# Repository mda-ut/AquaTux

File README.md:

AquaTux

Repository for University of Toronto's Mechatronics Design Association, which houses all revision controlled software and hardware for our team's entry into the international RoboSub competition: AquaTux!

See http://www.auvsifoundation.org/foundation/competitions/robosub/ for more detail on the competition. Also, our non revision controlled resources can be found at: https://www.dropbox.com/sh/x1nmdbmocld3edr/AAAKEdywBxVcvkEa93l7Mutga. See http://mda.markharfouche.com for our wiki, which is helpful for getting started with this repo.

Happy swimming!

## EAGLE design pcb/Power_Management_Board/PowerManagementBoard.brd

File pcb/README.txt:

Directory: root
Use: Should hold all the MDA PCB projects
Author: Mark Harfouche
Editors:

Every unique board should have it's own directory.
Updated revisions of an existing board should be kept in originals directory. 

Unlike what Mark had previously stated. We support both EAGLE and ALTIUM for PCB development. Pick your poison. 

Do not commit generated files such as Gerbers unless they are final revisions. 

-- David Biancolin (Dec, 2012)

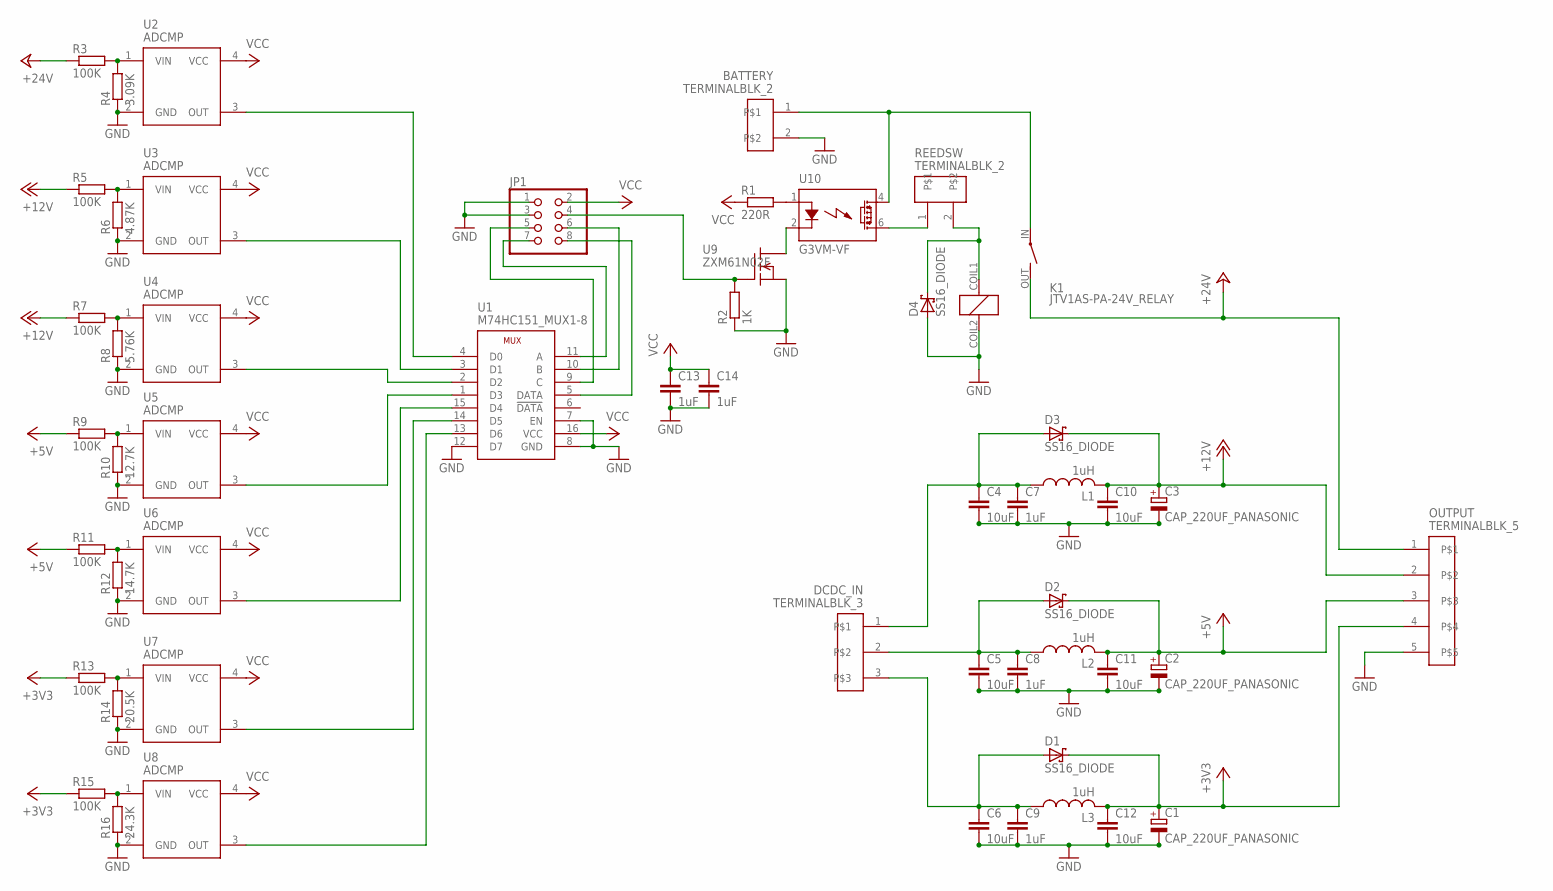
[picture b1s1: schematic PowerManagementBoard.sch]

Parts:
BATTERY: TERMINALBLK_2; TERMINAL_BLK-2
C1, C2, C3: CAP_220UF_PANASONIC
C4, C5, C6, C10, C11, C12: 10uF; C1206
C7, C8, C9, C13, C14: 1uF; C1206
D1, D2, D3, D4: SS16_DIODE; DO214AC
DCDC_IN: TERMINALBLK_3; TERMINAL_BLK-3
JP1: PINHD-2X4; 2X04
K1: JTV1AS-PA-24V_RELAY; JTV-RELAY_FORM1A
L1, L2, L3: 1uH; CHOKE_WE-HCC_8070
OUTPUT: TERMINALBLK_5; TERMINAL_BLK-5
R1: 220R; R0603
R2: 1K; R0603
R3, R5, R7, R9, R11, R13, R15: 100K; R0603
R4: 3.09K; R0603
R6: 4.87K; R0603
R8: 5.76K; R0603
R10: 12.7K; R0603
R12: 14.7K; R0603
R14: 20.5K; R0603
R16: 24.3K; R0603
REEDSW: TERMINALBLK_2; TERMINAL_BLK-2
U1: M74HC151_MUX1-8; TSSOP16
U2, U3, U4, U5, U6, U7, U8: ADCMP; SC70-4
U9: ZXM61N02F; SOT23W
U10: G3VM-VF

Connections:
+3V3: C1.P (+), C12.1, D1.C, L3.P$2 (2), OUTPUT.4, R13.1, R15.1
+5V: C2.P (+), C11.1, D2.C, L2.P$2 (2), OUTPUT.3, R9.1, R11.1
+12V: C3.P (+), C10.1, D3.C, L1.P$2 (2), OUTPUT.2, R5.1, R7.1
+24V: K1.OUT (S), OUTPUT.1, R3.1
GND: BATTERY.2, C1.N (-), C2.N (-), C3.N (-), C4.2, C5.2, C6.2, C7.2, C8.2, C9.2, C10.2, C11.2, C12.2, C13.2, C14.2, D4.A, JP1.1, JP1.3, K1.COIL2 (2), OUTPUT.5, R2.1, R4.1, R6.1, R8.1, R10.1, R12.1, R14.1, R16.1, U1.7 (EN), U1.8 (GND), U1.12 (D7), U2.2 (GND), U3.2 (GND), U4.2 (GND), U5.2 (GND), U6.2 (GND), U7.2 (GND), U8.2 (GND), U9.2 (S)
unnamed: BATTERY.1, K1.IN, U10.4 (DS1)
unnamed: REEDSW.1, U10.6 (DS2)
unnamed: D4.C, K1.COIL1 (1), REEDSW.2
unnamed: C6.1, C9.1, D1.A, DCDC_IN.3, L3.P$1 (1)
unnamed: C5.1, C8.1, D2.A, DCDC_IN.2, L2.P$1 (1)
unnamed: C4.1, C7.1, D3.A, DCDC_IN.1, L1.P$1 (1)
unnamed: U9.3 (D), U10.2 (K)
unnamed: R1.2, U10.1 (A)
unnamed: JP1.4, R2.2, U9.1 (G)
unnamed: JP1.8, U1.5 (DATA)
unnamed: JP1.6, U1.10 (B)
unnamed: JP1.7, U1.11 (A)
unnamed: JP1.5, U1.9 (C)
unnamed: R3.2, R4.2, U2.1 (VIN)
unnamed: R5.2, R6.2, U3.1 (VIN)
unnamed: R7.2, R8.2, U4.1 (VIN)
unnamed: R9.2, R10.2, U5.1 (VIN)
unnamed: R11.2, R12.2, U6.1 (VIN)
unnamed: R13.2, R14.2, U7.1 (VIN)
unnamed: R15.2, R16.2, U8.1 (VIN)
unnamed: U1.4 (D0), U2.3 (OUT)
unnamed: U1.3 (D1), U3.3 (OUT)
unnamed: U1.2 (D2), U4.3 (OUT)
unnamed: U1.1 (D3), U5.3 (OUT)
unnamed: U1.15 (D4), U6.3 (OUT)
unnamed: U1.14 (D5), U7.3 (OUT)
unnamed: U1.13 (D6), U8.3 (OUT)
VCC: C13.1, C14.1, JP1.2, R1.1, U1.16 (VCC), U2.4 (VCC), U3.4 (VCC), U4.4 (VCC), U5.4 (VCC), U6.4 (VCC), U7.4 (VCC), U8.4 (VCC)

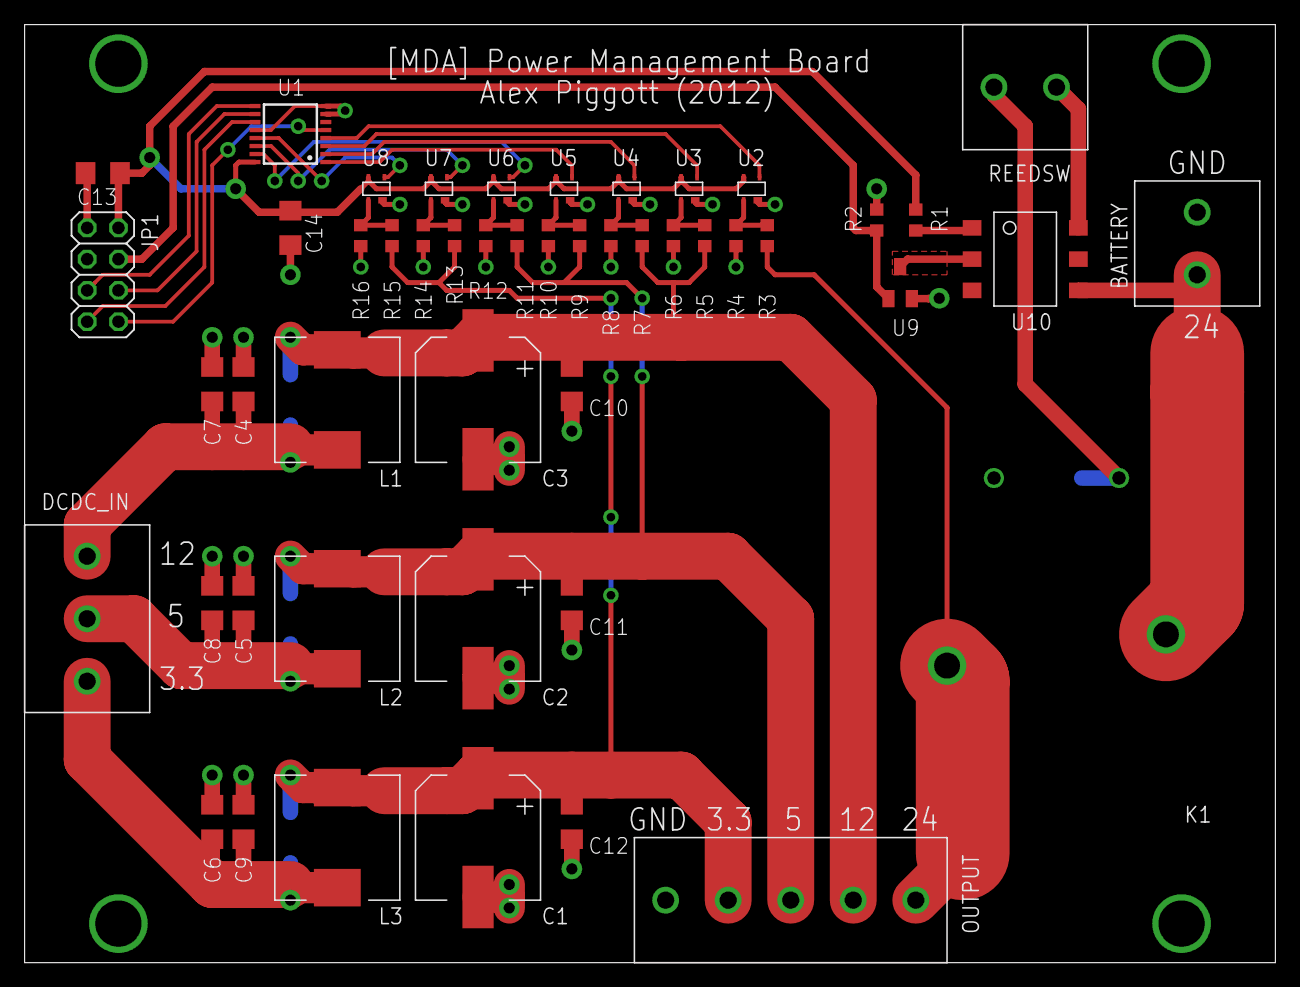
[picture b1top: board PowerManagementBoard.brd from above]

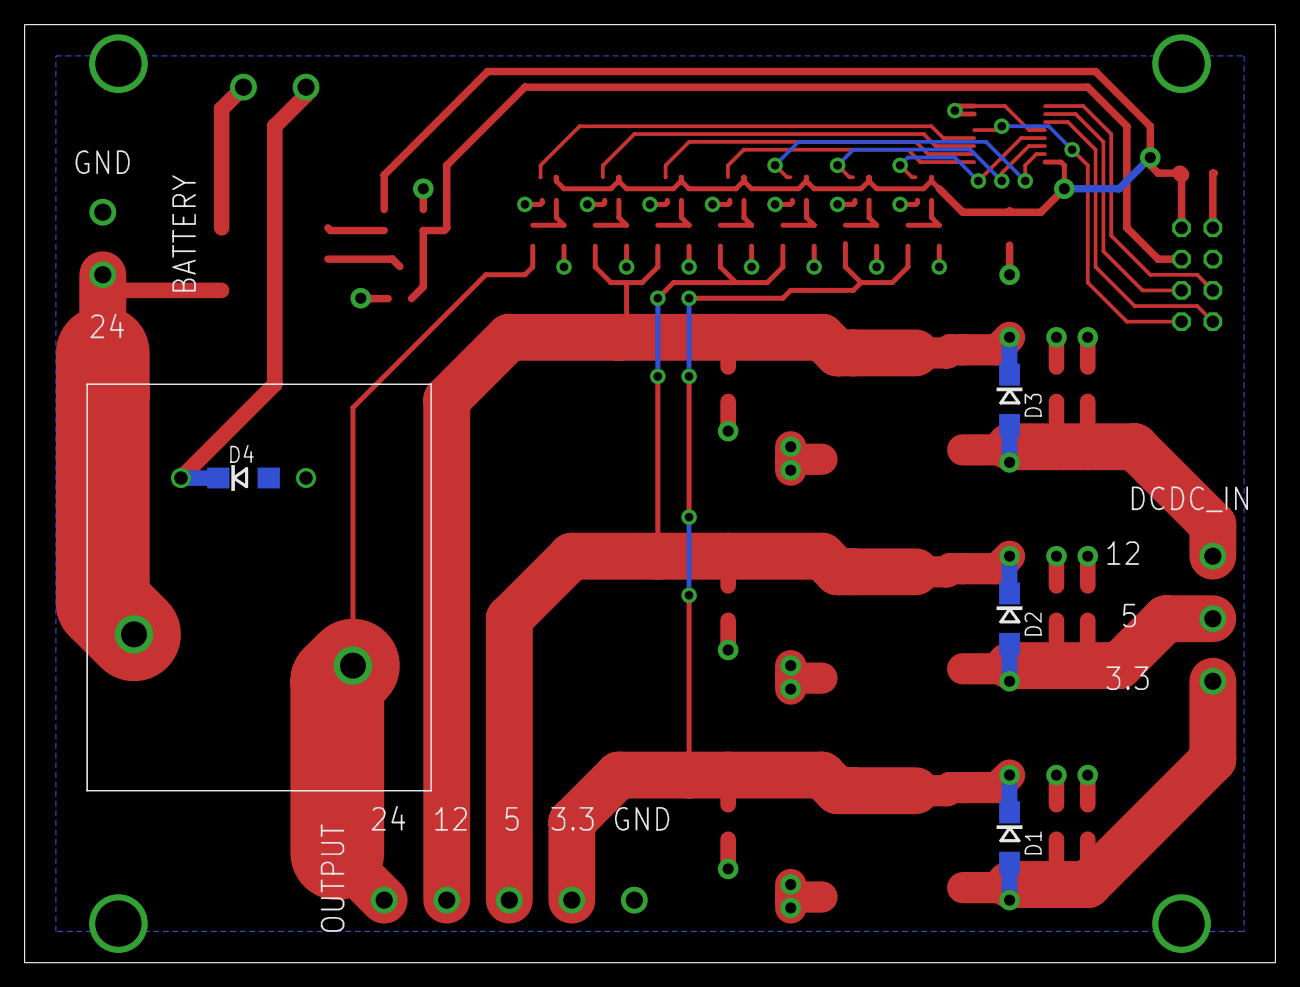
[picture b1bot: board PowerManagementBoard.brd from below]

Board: 2 copper layers, 101.6 x 76.2 mm, 53 parts (4 on the bottom side), 33 nets.

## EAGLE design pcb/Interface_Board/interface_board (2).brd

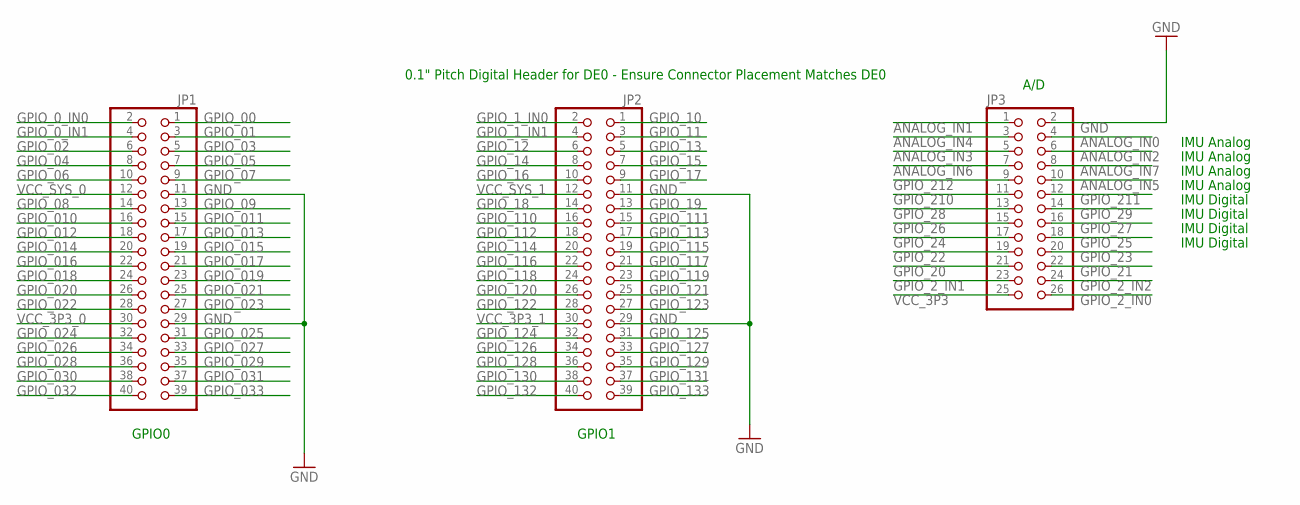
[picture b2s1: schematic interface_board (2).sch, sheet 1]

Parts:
JP1, JP2: PINHD-2X20; 2X20
JP3: PINHD-2X13; 2X13

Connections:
ANALOG_IN0: JP3.4; also elsewhere on the board
ANALOG_IN1: JP3.1; also elsewhere on the board
ANALOG_IN2: JP3.6; also elsewhere on the board
ANALOG_IN3: JP3.5; also elsewhere on the board
ANALOG_IN4: JP3.3; also elsewhere on the board
ANALOG_IN5: JP3.10; also elsewhere on the board
ANALOG_IN6: JP3.7; also elsewhere on the board
ANALOG_IN7: JP3.8; also elsewhere on the board
GND: JP1.11, JP1.29, JP2.11, JP2.29, JP3.2; also elsewhere on the board
GPIO_00: JP1.1; also elsewhere on the board
GPIO_0_IN0: JP1.2; also elsewhere on the board
GPIO_0_IN1: JP1.4; also elsewhere on the board
GPIO_01: JP1.3; also elsewhere on the board
GPIO_1_IN0: JP2.2; also elsewhere on the board
GPIO_1_IN1: JP2.4; also elsewhere on the board
GPIO_02: JP1.6; also elsewhere on the board
GPIO_2_IN0: JP3.26; also elsewhere on the board
GPIO_2_IN1: JP3.23; also elsewhere on the board
GPIO_2_IN2: JP3.24; also elsewhere on the board
GPIO_03: JP1.5; also elsewhere on the board
GPIO_04: JP1.8; also elsewhere on the board
GPIO_05: JP1.7; also elsewhere on the board
GPIO_06: JP1.10; also elsewhere on the board
GPIO_07: JP1.9; also elsewhere on the board
GPIO_08: JP1.14; also elsewhere on the board
GPIO_09: JP1.13; also elsewhere on the board
GPIO_010: JP1.16; also elsewhere on the board
GPIO_10: JP2.1; also elsewhere on the board
GPIO_011: JP1.15; also elsewhere on the board
GPIO_11: JP2.3; also elsewhere on the board
GPIO_012: JP1.18; also elsewhere on the board
GPIO_12: JP2.6; also elsewhere on the board
GPIO_013: JP1.17; also elsewhere on the board
GPIO_13: JP2.5; also elsewhere on the board
GPIO_014: JP1.20; also elsewhere on the board
GPIO_14: JP2.8; also elsewhere on the board
GPIO_015: JP1.19; also elsewhere on the board
GPIO_15: JP2.7; also elsewhere on the board
GPIO_016: JP1.22; also elsewhere on the board
GPIO_16: JP2.10; also elsewhere on the board
GPIO_017: JP1.21; also elsewhere on the board
GPIO_17: JP2.9; also elsewhere on the board
GPIO_018: JP1.24; also elsewhere on the board
GPIO_18: JP2.14; also elsewhere on the board
GPIO_019: JP1.23; also elsewhere on the board
GPIO_19: JP2.13; also elsewhere on the board
GPIO_020: JP1.26; also elsewhere on the board
GPIO_20: JP3.21; also elsewhere on the board
GPIO_021: JP1.25; also elsewhere on the board
GPIO_21: JP3.22; also elsewhere on the board
GPIO_022: JP1.28; also elsewhere on the board
GPIO_22: JP3.19; also elsewhere on the board
GPIO_023: JP1.27; also elsewhere on the board
GPIO_23: JP3.20; also elsewhere on the board
GPIO_024: JP1.32; also elsewhere on the board
GPIO_24: JP3.17; also elsewhere on the board
GPIO_025: JP1.31; also elsewhere on the board
GPIO_25: JP3.18; also elsewhere on the board
GPIO_026: JP1.34; also elsewhere on the board
GPIO_26: JP3.15; also elsewhere on the board
GPIO_027: JP1.33; also elsewhere on the board
GPIO_27: JP3.16; also elsewhere on the board
GPIO_028: JP1.36; also elsewhere on the board
GPIO_28: JP3.13; also elsewhere on the board
GPIO_029: JP1.35; also elsewhere on the board
GPIO_29: JP3.14; also elsewhere on the board
GPIO_030: JP1.38; also elsewhere on the board
GPIO_031: JP1.37; also elsewhere on the board
GPIO_032: JP1.40; also elsewhere on the board
GPIO_033: JP1.39; also elsewhere on the board
GPIO_110: JP2.16; also elsewhere on the board
GPIO_111: JP2.15; also elsewhere on the board
GPIO_112: JP2.18; also elsewhere on the board
GPIO_113: JP2.17; also elsewhere on the board
GPIO_114: JP2.20; also elsewhere on the board
GPIO_115: JP2.19; also elsewhere on the board
GPIO_116: JP2.22; also elsewhere on the board
GPIO_117: JP2.21; also elsewhere on the board
GPIO_118: JP2.24; also elsewhere on the board
GPIO_119: JP2.23; also elsewhere on the board
GPIO_120: JP2.26; also elsewhere on the board
GPIO_121: JP2.25; also elsewhere on the board
GPIO_122: JP2.28; also elsewhere on the board
GPIO_123: JP2.27; also elsewhere on the board
GPIO_124: JP2.32; also elsewhere on the board
GPIO_125: JP2.31; also elsewhere on the board
GPIO_126: JP2.34; also elsewhere on the board
GPIO_127: JP2.33; also elsewhere on the board
GPIO_128: JP2.36; also elsewhere on the board
GPIO_129: JP2.35; also elsewhere on the board
GPIO_130: JP2.38; also elsewhere on the board
GPIO_131: JP2.37; also elsewhere on the board
GPIO_132: JP2.40; also elsewhere on the board
GPIO_133: JP2.39; also elsewhere on the board
GPIO_210: JP3.11; also elsewhere on the board
GPIO_211: JP3.12; also elsewhere on the board
GPIO_212: JP3.9; also elsewhere on the board
VCC_3P3: JP3.25; also elsewhere on the board
VCC_3P3_0: JP1.30
VCC_3P3_1: JP2.30; also elsewhere on the board
VCC_SYS_0: JP1.12
VCC_SYS_1: JP2.12

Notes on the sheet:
0.1" Pitch Digital Header for DE0 - Ensure Connector Placement Matches DE0
GPIO0
GPIO1
A/D
IMU Analog
IMU Digital

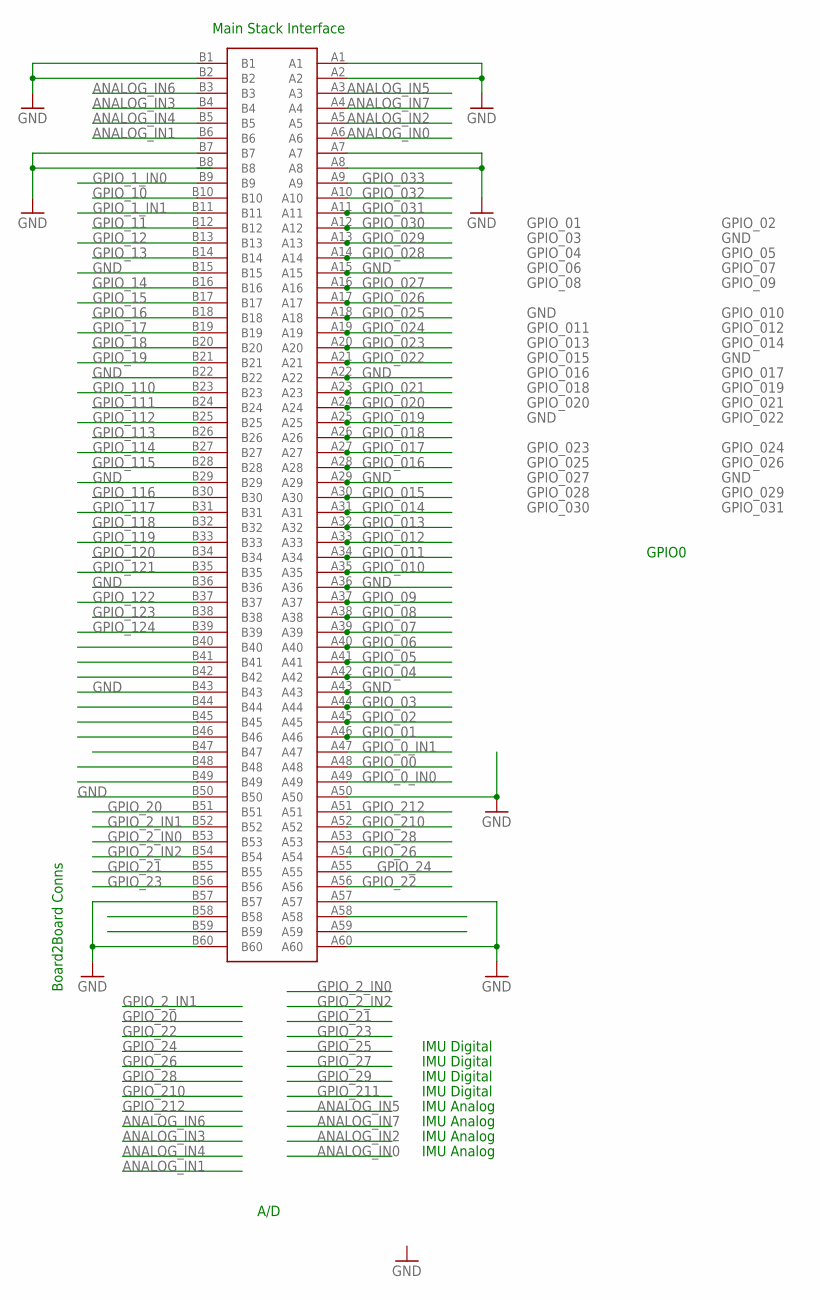
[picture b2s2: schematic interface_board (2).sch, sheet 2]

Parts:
U$10: MAIN-STACK-CONN-WIDEPITCH; STACK-CONN-WIDEPITCH

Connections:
ANALOG_IN0: U$10.A6; also elsewhere on the board
ANALOG_IN1: U$10.B6; also elsewhere on the board
ANALOG_IN2: U$10.A5; also elsewhere on the board
ANALOG_IN3: U$10.B4; also elsewhere on the board
ANALOG_IN4: U$10.B5; also elsewhere on the board
ANALOG_IN5: U$10.A3; also elsewhere on the board
ANALOG_IN6: U$10.B3; also elsewhere on the board
ANALOG_IN7: U$10.A4; also elsewhere on the board
GND: U$10.A1, U$10.A2, U$10.A7, U$10.A8, U$10.A15, U$10.A22, U$10.A29, U$10.A36, U$10.A43, U$10.A50, U$10.A57, U$10.A60, U$10.B1, U$10.B2, U$10.B7, U$10.B15, U$10.B22, U$10.B29, U$10.B36, U$10.B43, U$10.B50, U$10.B57, U$10.B60; also elsewhere on the board
GPIO_00: U$10.A48; also elsewhere on the board
GPIO_0_IN0: U$10.A49; also elsewhere on the board
GPIO_0_IN1: U$10.A47; also elsewhere on the board
GPIO_01: U$10.A46; also elsewhere on the board
GPIO_1_IN0: U$10.B9; also elsewhere on the board
GPIO_1_IN1: U$10.B11; also elsewhere on the board
GPIO_02: U$10.A45; also elsewhere on the board
GPIO_2_IN0: U$10.B53; also elsewhere on the board
GPIO_2_IN1: U$10.B52; also elsewhere on the board
GPIO_2_IN2: U$10.B54; also elsewhere on the board
GPIO_03: U$10.A44; also elsewhere on the board
GPIO_04: U$10.A42; also elsewhere on the board
GPIO_05: U$10.A41; also elsewhere on the board
GPIO_06: U$10.A40; also elsewhere on the board
GPIO_07: U$10.A39; also elsewhere on the board
GPIO_08: U$10.A38; also elsewhere on the board
GPIO_09: U$10.A37; also elsewhere on the board
GPIO_010: U$10.A35; also elsewhere on the board
GPIO_10: U$10.B10; also elsewhere on the board
GPIO_011: U$10.A34; also elsewhere on the board
GPIO_11: U$10.B12; also elsewhere on the board
GPIO_012: U$10.A33; also elsewhere on the board
GPIO_12: U$10.B13; also elsewhere on the board
GPIO_013: U$10.A32; also elsewhere on the board
GPIO_13: U$10.B14; also elsewhere on the board
GPIO_014: U$10.A31; also elsewhere on the board
GPIO_14: U$10.B16; also elsewhere on the board
GPIO_015: U$10.A30; also elsewhere on the board
GPIO_15: U$10.B17; also elsewhere on the board
GPIO_016: U$10.A28; also elsewhere on the board
GPIO_16: U$10.B18; also elsewhere on the board
GPIO_017: U$10.A27; also elsewhere on the board
GPIO_17: U$10.B19; also elsewhere on the board
GPIO_018: U$10.A26; also elsewhere on the board
GPIO_18: U$10.B20; also elsewhere on the board
GPIO_019: U$10.A25; also elsewhere on the board
GPIO_19: U$10.B21; also elsewhere on the board
GPIO_020: U$10.A24; also elsewhere on the board
GPIO_20: U$10.B51; also elsewhere on the board
GPIO_021: U$10.A23; also elsewhere on the board
GPIO_21: U$10.B55; also elsewhere on the board
GPIO_022: U$10.A21; also elsewhere on the board
GPIO_22: U$10.A56; also elsewhere on the board
GPIO_023: U$10.A20; also elsewhere on the board
GPIO_23: U$10.B56; also elsewhere on the board
GPIO_024: U$10.A19; also elsewhere on the board
GPIO_24: U$10.A55; also elsewhere on the board
GPIO_025: U$10.A18; also elsewhere on the board
GPIO_026: U$10.A17; also elsewhere on the board
GPIO_26: U$10.A54; also elsewhere on the board
GPIO_027: U$10.A16; also elsewhere on the board
GPIO_028: U$10.A14; also elsewhere on the board
GPIO_28: U$10.A53; also elsewhere on the board
GPIO_029: U$10.A13; also elsewhere on the board
GPIO_030: U$10.A12; also elsewhere on the board
GPIO_031: U$10.A11; also elsewhere on the board
GPIO_032: U$10.A10; also elsewhere on the board
GPIO_033: U$10.A9; also elsewhere on the board
GPIO_110: U$10.B23; also elsewhere on the board
GPIO_111: U$10.B24; also elsewhere on the board
GPIO_112: U$10.B25; also elsewhere on the board
GPIO_113: U$10.B26; also elsewhere on the board
GPIO_114: U$10.B27; also elsewhere on the board
GPIO_115: U$10.B28; also elsewhere on the board
GPIO_116: U$10.B30; also elsewhere on the board
GPIO_117: U$10.B31; also elsewhere on the board
GPIO_118: U$10.B32; also elsewhere on the board
GPIO_119: U$10.B33; also elsewhere on the board
GPIO_120: U$10.B34; also elsewhere on the board
GPIO_121: U$10.B35; also elsewhere on the board
GPIO_122: U$10.B37; also elsewhere on the board
GPIO_123: U$10.B38; also elsewhere on the board
GPIO_124: U$10.B39; also elsewhere on the board
GPIO_210: U$10.A52; also elsewhere on the board
GPIO_212: U$10.A51; also elsewhere on the board

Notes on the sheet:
Main Stack Interface
GPIO0
A/D
IMU Analog
IMU Digital
Board2Board Conns

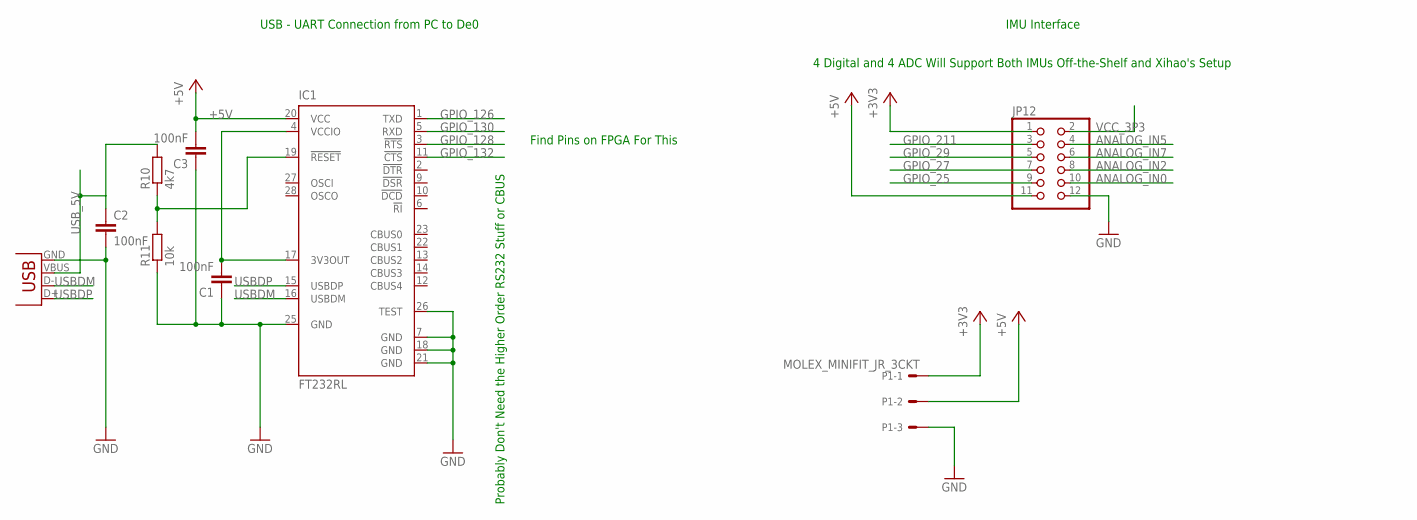
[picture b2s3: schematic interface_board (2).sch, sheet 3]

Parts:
C1, C2, C3: 100nF; C0805
IC1: FT232RL; SSOP28
JP12: PINHD-2X6; 2X06
P1: MOLEX_MINIFIT_JR_3CKT; 3CKT_MINIFIT_JR
R10: 4k7; M0805
R11: 10k; M0805
X1: USBSMD; USB-MINIB

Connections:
+3V3: JP12.1, P1.1; also elsewhere on the board
+5V: C3.2, IC1.20 (VCC), JP12.11, P1.2
ANALOG_IN0: JP12.10; also elsewhere on the board
ANALOG_IN2: JP12.8; also elsewhere on the board
ANALOG_IN5: JP12.4; also elsewhere on the board
ANALOG_IN7: JP12.6; also elsewhere on the board
GND: C1.1, C2.2, C3.1, IC1.7 (GND), IC1.18 (GND), IC1.21 (GND), IC1.25 (GND), IC1.26 (TEST), JP12.12, P1.3, R11.1, X1.GND; also elsewhere on the board
GPIO_25: JP12.9; also elsewhere on the board
GPIO_27: JP12.7; also elsewhere on the board
GPIO_29: JP12.5; also elsewhere on the board
GPIO_126: IC1.1 (TXD); also elsewhere on the board
GPIO_128: IC1.3 (!RTS); also elsewhere on the board
GPIO_130: IC1.5 (RXD); also elsewhere on the board
GPIO_132: IC1.11 (!CTS); also elsewhere on the board
GPIO_211: JP12.3; also elsewhere on the board
unnamed: C1.2, IC1.4 (VCCIO), IC1.17 (3V3OUT)
unnamed: IC1.19 (!RESET), R10.1, R11.2
USBDM: IC1.16 (USBDM), X1.D-
USBDP: IC1.15 (USBDP), X1.D+
USB_5V: C2.1, R10.2, X1.VBUS
VCC_3P3: JP12.2; also elsewhere on the board

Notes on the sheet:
USB - UART Connection from PC to De0
IMU Interface
Probably Don't Need the Higher Order RS232 Stuff or CBUS
Find Pins on FPGA For This
4 Digital and 4 ADC Will Support Both IMUs Off-the-Shelf and Xihao's Setup

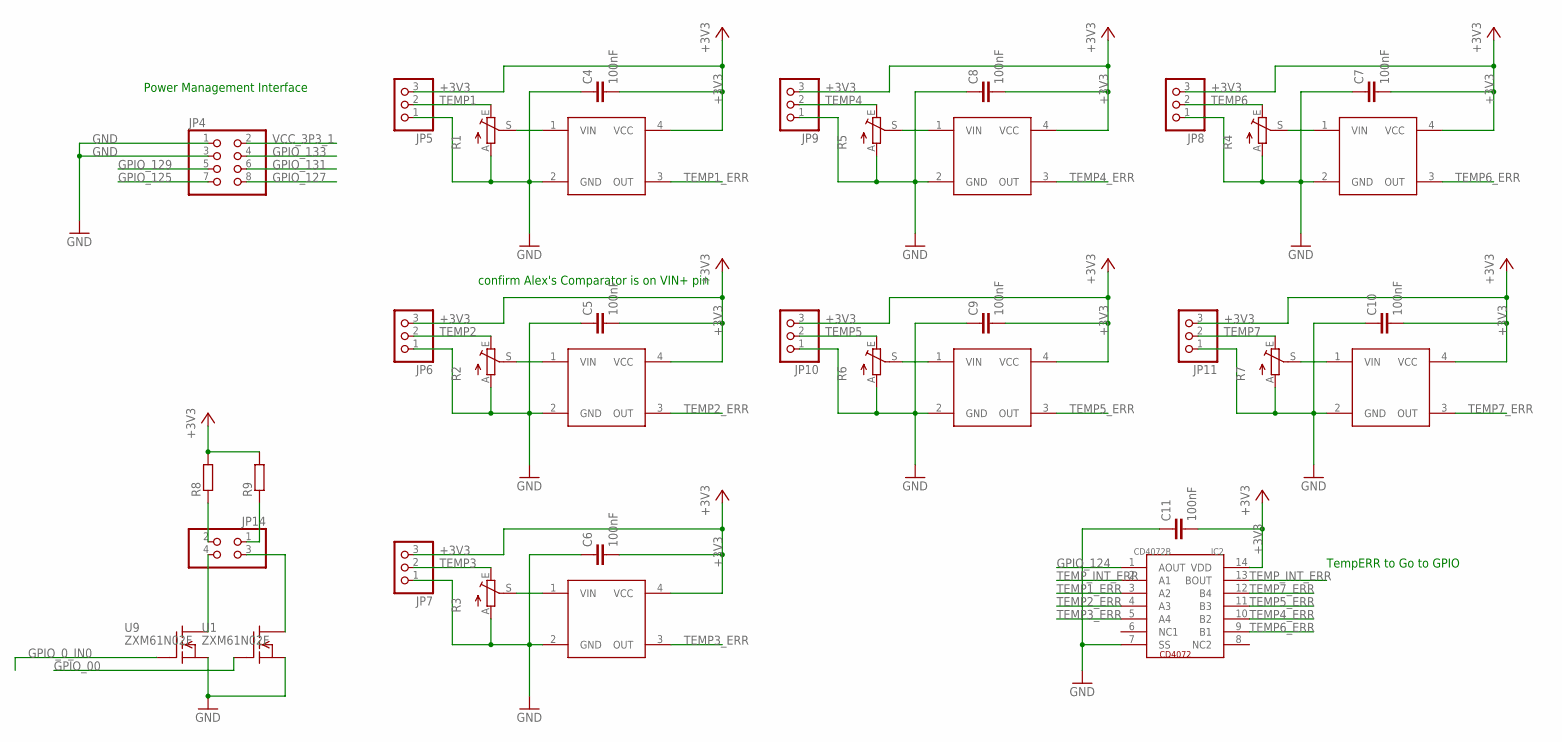
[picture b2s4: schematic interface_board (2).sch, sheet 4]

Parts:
C4, C5, C6, C7, C8, C9, C10, C11: 100nF; C0805
IC2: CD4072B; SO14
JP4: PINHD-2X4; 2X04
JP5, JP6, JP7, JP8, JP9, JP10, JP11: PINHD-1X3; 1X03
JP14: PINHD-2X2; 2X02
R1, R2, R3, R4, R5, R6, R7: TRIM_1234-S64YW; POT
R8, R9: R-EU_M1206; M1206
U1, U9: ZXM61N02F; SOT23W
U$2, U$4, U$5, U$6, U$7, U$8, U$9: ADCMP

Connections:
+3V3: C4.2, C5.2, C6.2, C7.2, C8.2, C9.2, C10.2, C11.2, IC2.14 (VDD), JP5.3, JP6.3, JP7.3, JP8.3, JP9.3, JP10.3, JP11.3, R8.2, R9.2, U$2.4 (VCC), U$4.4 (VCC), U$5.4 (VCC), U$6.4 (VCC), U$7.4 (VCC), U$8.4 (VCC), U$9.4 (VCC); also elsewhere on the board
GND: C4.1, C5.1, C6.1, C7.1, C8.1, C9.1, C10.1, C11.1, IC2.7 (SS), JP4.1, JP4.3, JP5.1, JP6.1, JP7.1, JP8.1, JP9.1, JP10.1, JP11.1, R1.A, R2.A, R3.A, R4.A, R5.A, R6.A, R7.A, U1.2 (S), U9.2 (S), U$2.2 (GND), U$4.2 (GND), U$5.2 (GND), U$6.2 (GND), U$7.2 (GND), U$8.2 (GND), U$9.2 (GND); also elsewhere on the board
GPIO_00: U1.1 (G); also elsewhere on the board
GPIO_0_IN0: U9.1 (G); also elsewhere on the board
GPIO_124: IC2.1 (AOUT); also elsewhere on the board
GPIO_125: JP4.7; also elsewhere on the board
GPIO_127: JP4.8; also elsewhere on the board
GPIO_129: JP4.5; also elsewhere on the board
GPIO_131: JP4.6; also elsewhere on the board
GPIO_133: JP4.4; also elsewhere on the board
unnamed: R1.S, U$2.1 (VIN)
unnamed: R2.S, U$4.1 (VIN)
unnamed: R3.S, U$5.1 (VIN)
unnamed: R4.S, U$6.1 (VIN)
unnamed: R5.S, U$7.1 (VIN)
unnamed: R6.S, U$8.1 (VIN)
unnamed: R7.S, U$9.1 (VIN)
unnamed: JP14.2, R8.1
unnamed: JP14.4, U9.3 (D)
unnamed: JP14.1, R9.1
unnamed: JP14.3, U1.3 (D)
TEMP1: JP5.2, R1.E
TEMP1_ERR: IC2.3 (A2), U$2.3 (OUT)
TEMP2: JP6.2, R2.E
TEMP2_ERR: IC2.4 (A3), U$4.3 (OUT)
TEMP3: JP7.2, R3.E
TEMP3_ERR: IC2.5 (A4), U$5.3 (OUT)
TEMP4: JP9.2, R5.E
TEMP4_ERR: IC2.10 (B2), U$7.3 (OUT)
TEMP5: JP10.2, R6.E
TEMP5_ERR: IC2.11 (B3), U$8.3 (OUT)
TEMP6: JP8.2, R4.E
TEMP6_ERR: IC2.9 (B1), U$6.3 (OUT)
TEMP7: JP11.2, R7.E
TEMP7_ERR: IC2.12 (B4), U$9.3 (OUT)
TEMP_INT_ERR: IC2.2 (A1), IC2.13 (BOUT)
VCC_3P3_1: JP4.2; also elsewhere on the board

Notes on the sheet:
Power Management Interface
TempERR to Go to GPIO
confirm Alex's Comparator is on VIN+ pin

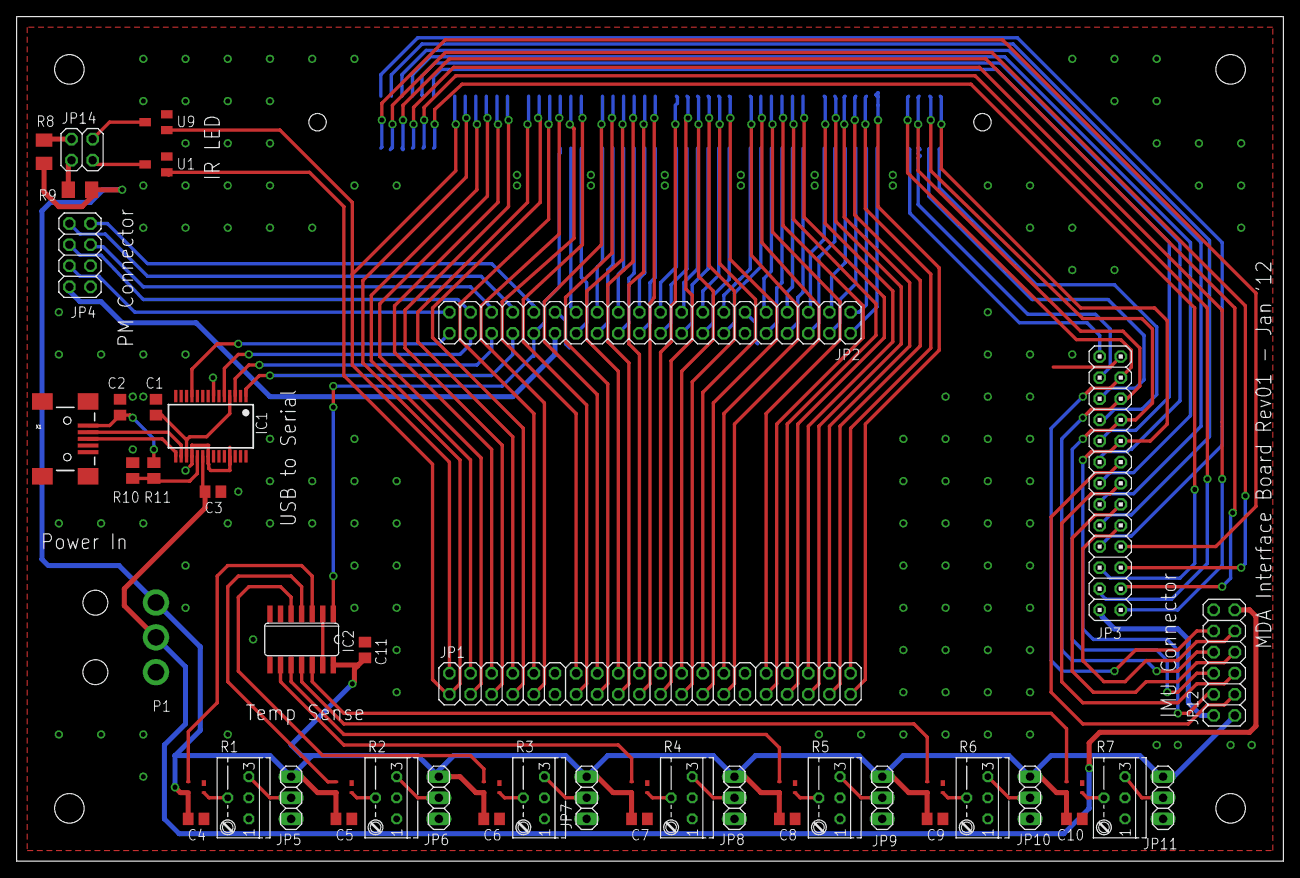
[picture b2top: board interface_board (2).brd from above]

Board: 2 copper layers, 152.4 x 101.6 mm, 49 parts (1 on the bottom side), 132 nets.
